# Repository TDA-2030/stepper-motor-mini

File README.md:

# Stepper Motor mini

A very simple and low-cost  stepper motor controller based on [dummy robot](https://gitee.com/switchpi/dummy)

## How to build

build on Windows

1. Download toolchain from https://github.com/xpack-dev-tools/arm-none-eabi-gcc-xpack/releases and unzip it.
2. run follow command to build
    ```shell
    mkdir build
    cmake -G "MinGW Makefiles" ..
    ```

## Feature

- Power: 12v~24v
- 2-layer board
- mini size
- Modbus support

## Preview

<center>
<figure>

·
·
·

</figure>
</center>

## Uasge

### Button Functions

| Action     | Function              |
| ---------- | --------------------- |
| click      | toggle to run or stop |
| long press | restore settings      |

### calibration

push down the button then power on, the motor well start to calibration sensor.

### Modbus Register

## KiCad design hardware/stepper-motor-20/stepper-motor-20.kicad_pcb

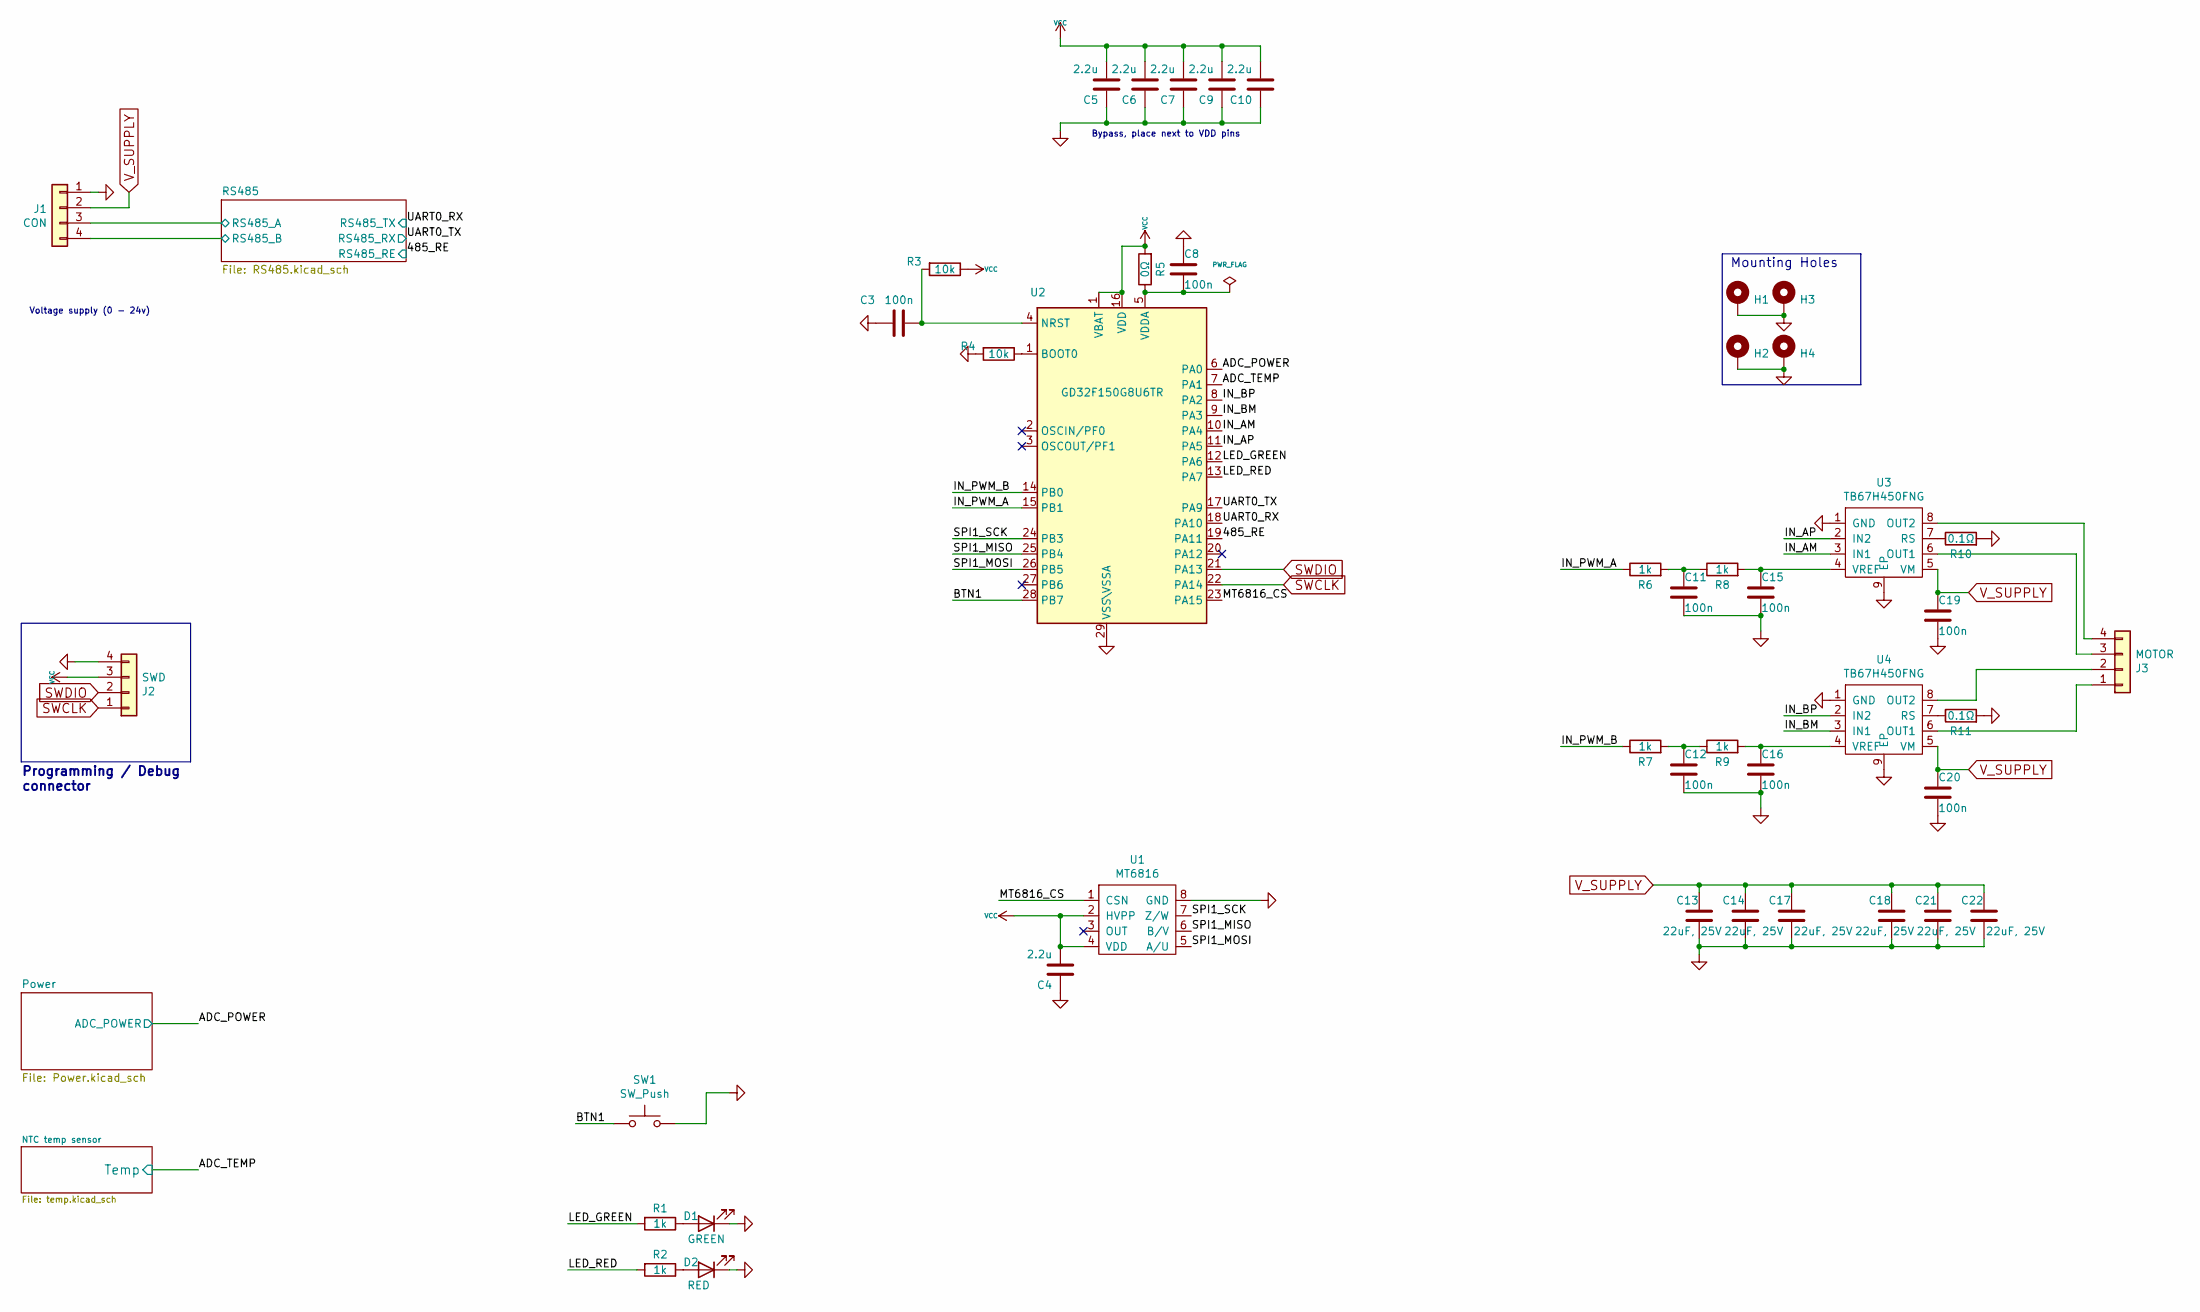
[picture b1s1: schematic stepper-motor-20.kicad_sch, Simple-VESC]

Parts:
C3, C8, C11, C12, C15, C16, C19, C20: 100n; C_0402_1005Metric
C4, C5, C6, C7, C9, C10: 2.2u; C_0402_1005Metric
C13, C14, C17, C18, C21, C22: 22uF, 25V; C_1206_3216Metric
D1: GREEN; LED_0402_1005Metric
D2: RED; LED_0402_1005Metric
H1, H2, H3, H4: MountingHole_Pad; MountingHole_2.0mm_Pad_Via
J1: CON; PinHeader_1x04_P2.00mm_Vertical
J2: SWD; PinHeader_1x04_P1.00mm_Vertical
J3: MOTOR; PinHeader_1x04_P2.00mm_Vertical
R1, R2, R6, R7, R8, R9: 1k; R_0402_1005Metric
R3, R4: 10k; R_0402_1005Metric
R5: 0Ω; R_0402_1005Metric
R10, R11: 0.1Ω; R_0805_2012Metric
SW1: SW_Push; SW_Push_SPST_NO_Alps_SKRK
U1: MT6816; SOP-8_3.76x4.96mm_P1.27mm
U2: GD32F150G8U6TR; QFN-28-1EP_4x4mm_P0.4mm_EP2.6x2.6mm
U3, U4: TB67H450FNG; SOIC-8-1EP_3.9x4.9mm_P1.27mm_EP2.41x3.3mm

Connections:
/485_RE: U2.19 (PA11); also elsewhere on the board
/ADC_POWER: U2.6 (PA0); also elsewhere on the board
/ADC_TEMP: U2.7 (PA1); also elsewhere on the board
/BTN1: SW1.1, U2.28 (PB7)
/IN_AM: U2.10 (PA4), U3.3 (IN1)
/IN_AP: U2.11 (PA5), U3.2 (IN2)
/IN_BM: U2.9 (PA3), U4.3 (IN1)
/IN_BP: U2.8 (PA2), U4.2 (IN2)
/IN_PWM_A: R6.1, U2.15 (PB1)
/IN_PWM_B: R7.1, U2.14 (PB0)
/LED_GREEN: R1.2, U2.12 (PA6)
/LED_RED: R2.2, U2.13 (PA7)
/MT6816_CS: U1.1 (CSN), U2.23 (PA15)
/RS485/RS485_A: J1.3; also elsewhere on the board
/RS485/RS485_B: J1.4; also elsewhere on the board
/SPI1_MISO: U1.6 (B/V), U2.25 (PB4)
/SPI1_MOSI: U1.5 (A/U), U2.26 (PB5)
/SPI1_SCK: U1.7 (Z/W), U2.24 (PB3)
/UART0_RX: U2.18 (PA10); also elsewhere on the board
/UART0_TX: U2.17 (PA9); also elsewhere on the board
unnamed: C3.2, R3.2, U2.4 (NRST)
unnamed: C8.1, R5.1, U2.5 (VDDA)
unnamed: C11.2, R6.2, R8.1
unnamed: C12.2, R7.2, R9.1
unnamed: C15.2, R8.2, U3.4 (VREF)
unnamed: C16.2, R9.2, U4.4 (VREF)
unnamed: D1.2 (A), R1.1
unnamed: D2.2 (A), R2.1
unnamed: J3.1, U4.6 (OUT1)
unnamed: J3.2, U4.8 (OUT2)
unnamed: J3.3, U3.6 (OUT1)
unnamed: J3.4, U3.8 (OUT2)
unnamed: R10.1, U3.7 (RS)
unnamed: R11.1, U4.7 (RS)
SWCLK: J2.1, U2.22 (PA14)
SWDIO: J2.2, U2.21 (PA13)
V_SUPPLY: C13.2, C14.2, C17.2, C18.2, C19.2, C20.2, C21.2, C22.2, J1.2, U3.5 (VM), U4.5 (VM); also elsewhere on the board

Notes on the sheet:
Programming / Debug connector
Voltage supply (0 - 24v)
Mounting Holes
Bypass, place next to VDD pins

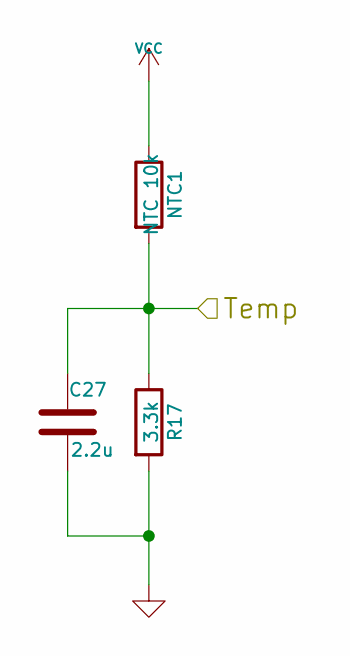
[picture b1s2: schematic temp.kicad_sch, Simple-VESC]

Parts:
C27: 2.2u; C_0402_1005Metric
NTC1: NTC 10k; R_0402_1005Metric
R17: 3.3k; R_0402_1005Metric

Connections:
/ADC_TEMP: C27.1, NTC1.2, R17.1; also elsewhere on the board

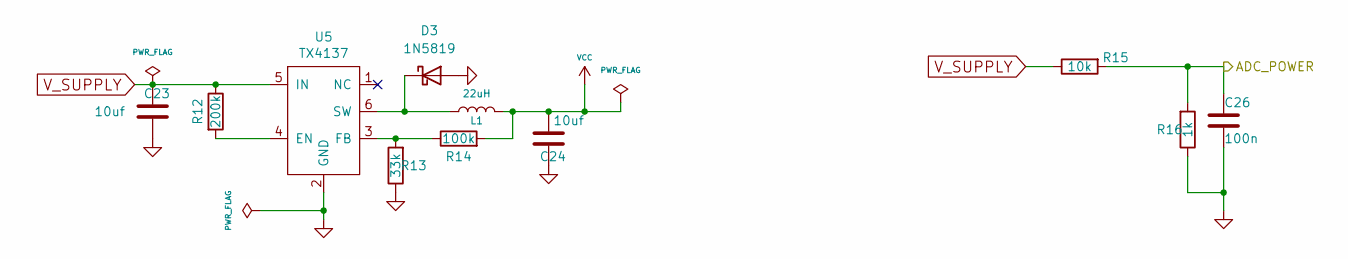
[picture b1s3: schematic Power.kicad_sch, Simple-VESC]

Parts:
C23, C24: 10uf; C_0603_1608Metric
C26: 100n; C_0402_1005Metric
D3: 1N5819; D_SOD-323
L1: 22uH; L_Taiyo-Yuden_MD-3030
R12: 200k; R_0402_1005Metric
R13: 33k; R_0402_1005Metric
R14: 100k; R_0402_1005Metric
R15: 10k; R_0402_1005Metric
R16: 1k; R_0402_1005Metric
U5: TX4137; SOT-23-6

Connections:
/ADC_POWER: C26.2, R15.2, R16.2; also elsewhere on the board
unnamed: D3.1 (K), L1.1, U5.6 (SW)
unnamed: R12.2, U5.4 (EN)
unnamed: R13.2, R14.1, U5.3 (FB)
V_SUPPLY: C23.2, R12.1, R15.1, U5.5 (IN); also elsewhere on the board

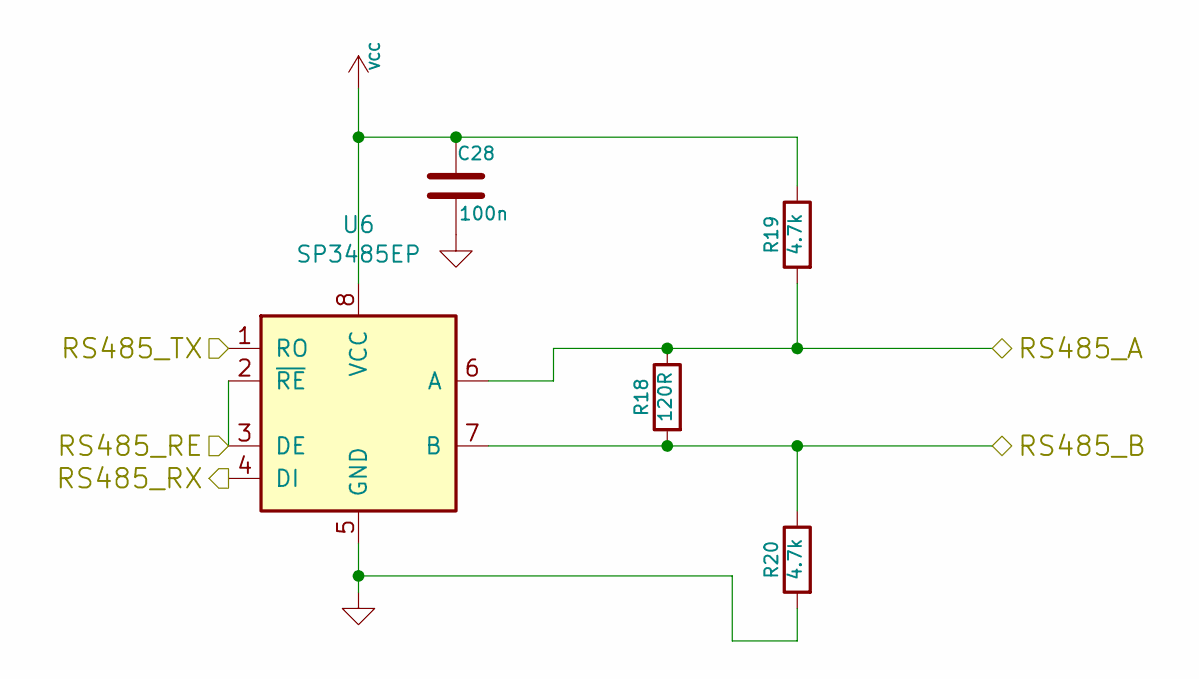
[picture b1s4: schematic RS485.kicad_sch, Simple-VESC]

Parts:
C28: 100n; C_0402_1005Metric
R18: 120R; R_0402_1005Metric
R19, R20: 4.7k; R_0402_1005Metric
U6: SP3485EP; SOIC-8_3.9x4.9mm_P1.27mm

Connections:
/485_RE: U6.2 (~RE), U6.3 (DE); also elsewhere on the board
/RS485/RS485_A: R18.1, R19.2, U6.6 (A); also elsewhere on the board
/RS485/RS485_B: R18.2, R20.1, U6.7 (B); also elsewhere on the board
/UART0_RX: U6.1 (RO); also elsewhere on the board
/UART0_TX: U6.4 (DI); also elsewhere on the board

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
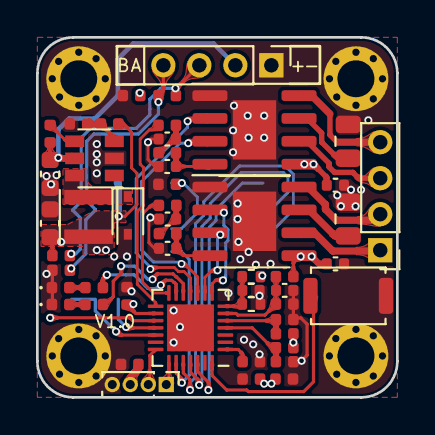
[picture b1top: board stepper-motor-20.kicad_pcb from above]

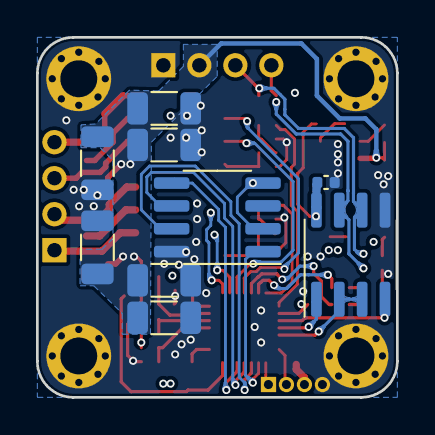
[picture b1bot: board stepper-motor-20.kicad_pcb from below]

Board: 4 copper layers, 20.0 x 20.0 mm, 64 parts (9 on the bottom side), 43 nets.

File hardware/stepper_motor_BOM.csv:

"Comment","Description","Designator","Footprint","LibRef","Pins","Quantity","PartNumber","url",
"15p","desc","C1,C2,","C_0402_1005Metric","libref","2","2","","",
"100n","desc","C3,C8,C11,C12,C15,C16,C19,C20,C28,C29,","C_0402_1005Metric","libref","2","10","","",
"2.2u","desc","C4,C5,C6,C7,C9,C10,C24,","C_0402_1005Metric","libref","2","7","","",
"10uf","desc","C25,C26,C27,","C_0603_1608Metric","libref","2","3","","",
"GREEN","desc","D1,","LED_0603_1608Metric","libref","2","1","","",
"RED","desc","D2,","LED_0603_1608Metric","libref","2","1","","",
"B5819W SL","desc","D3,","D_SOD-123","libref","2","1","","",
"22uH","desc","L1,","L_Taiyo-Yuden_NR-40xx","libref","2","1","","",
"1k","desc","R1,R2,R6,R7,R8,R9,R17,","R_0402_1005Metric","libref","2","7","","",
"10k","desc","R3,R4,R16,","R_0402_1005Metric","libref","2","3","","",
"0Ω","desc","R5,R21,R22,R23,","R_0402_1005Metric","libref","2","4","","",
"0.1Ω","desc","R10,R11,","R_0805_2012Metric","libref","2","2","","",
"3.3k","desc","R12,","R_0402_1005Metric","libref","2","1","","",
"200k","desc","R13,","R_0402_1005Metric","libref","2","1","","",
"33k","desc","R14,","R_0402_1005Metric","libref","2","1","","",
"100k","desc","R15,","R_0402_1005Metric","libref","2","1","","",
"120R","desc","R18,","R_0402_1005Metric","libref","2","1","","",
"360R","desc","R19,R20,","R_0402_1005Metric","libref","2","2","","",
"STM32F103CBTx","desc","U2,","LQFP-48_7x7mm_P0.5mm","libref","48","1","","",
"TB67H450FNG","desc","U3,U4,","SOIC-8-1EP_3.9x4.9mm_P1.27mm_EP2.41x3.3mm","libref","13","2","","",
"TX4137","desc","U5,","SOT-23-6","libref","6","1","","",
"8MHz","desc","Y1,","Crystal_SMD_3225-4Pin_3.2x2.5mm","libref","4","1","","",
"SW_Push","desc","SW2,SW3,","SW_Push_SPST_NO_Alps_SKRK","libref","2","2","","",
"22uF, 25V","desc","C13,C14,C17,C18,C21,C22,","C_1206_3216Metric","libref","2","6","","",
"MT6816","desc","U1,","SOIC-8_3.9x4.9mm_P1.27mm","libref","8","1","","",
"SP3485EP","desc","U6,","SOIC-8_3.9x4.9mm_P1.27mm","libref","8","1","","",
"NTC 10k","desc","NTC1,","R_0603_1608Metric","libref","2","1","","",
"Through Hole Items ",
"MountingHole_Pad","desc","H1,H2,H3,H4,","MountingHole_2.5mm_Pad_Via","libref","9","4","","",
"CON","desc","J1,","JST_PH_B4B-PH-K_1x04_P2.00mm_Vertical","libref","4","1","","",
"SWD","desc","J2,","PinHeader_1x04_P1.27mm_Vertical","libref","4","1","","",
"MOTOR","desc","J3,","PinHeader_1x04_P2.00mm_Vertical","libref","4","1","","",

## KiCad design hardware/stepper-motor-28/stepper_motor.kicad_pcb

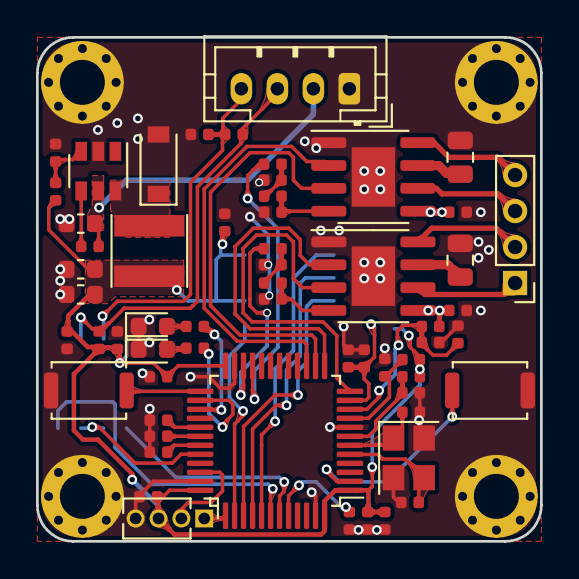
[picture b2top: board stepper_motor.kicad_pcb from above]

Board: 2 copper layers, 28.0 x 28.0 mm, 72 parts (0 on the bottom side), 49 nets.

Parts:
C1, C2: 15p; C_0402_1005Metric
C3, C8, C11, C12, C15, C16, C19, C20, C28, C29: 100n; C_0402_1005Metric
C4, C5, C6, C7, C9, C10, C24: 2.2u; C_0402_1005Metric
C13, C14, C17, C18, C21, C22: 22uF, 25V; C_1206_3216Metric
C25, C26, C27: 10uf; C_0603_1608Metric
D1: GREEN; LED_0603_1608Metric
D2: RED; LED_0603_1608Metric
D3: B5819W SL; D_SOD-123
H1, H2, H3, H4: MountingHole_Pad; MountingHole_2.5mm_Pad_Via
J1: CON; JST_PH_B4B-PH-K_1x04_P2.00mm_Vertical
J2: SWD; PinHeader_1x04_P1.27mm_Vertical
J3: MOTOR; PinHeader_1x04_P2.00mm_Vertical
L1: 22uH; L_Taiyo-Yuden_NR-40xx
NTC1: NTC 10k; R_0603_1608Metric
R1, R2, R6, R7, R8, R9, R17: 1k; R_0402_1005Metric
R3, R4, R16: 10k; R_0402_1005Metric
R5, R21, R22, R23: 0Ω; R_0402_1005Metric
R10, R11: 0.1Ω; R_0805_2012Metric
R12: 3.3k; R_0402_1005Metric
R13: 200k; R_0402_1005Metric
R14: 33k; R_0402_1005Metric
R15: 100k; R_0402_1005Metric
R18: 120R; R_0402_1005Metric
R19, R20: 360R; R_0402_1005Metric
SW2, SW3: SW_Push; SW_Push_SPST_NO_Alps_SKRK
U1: MT6816; SOIC-8_3.9x4.9mm_P1.27mm
U2: STM32F103CBTx; LQFP-48_7x7mm_P0.5mm
U3, U4: TB67H450FNG; SOIC-8-1EP_3.9x4.9mm_P1.27mm_EP2.41x3.3mm
U5: TX4137; SOT-23-6
U6: SP3485EP; SOIC-8_3.9x4.9mm_P1.27mm
Y1: 8MHz; Crystal_SMD_3225-4Pin_3.2x2.5mm

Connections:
/485_RE: U2.32, U6.2, U6.3
/ADC_POWER: C28.2, R16.2, R17.2, U2.10
/ADC_TEMP: C24.1, NTC1.2, R12.1, U2.11
/BTN1: SW3.1, U2.25
/BTN2: SW2.1, U2.2
/ID0: R21.1, U2.29
/ID1: R22.1, U2.30
/ID2: R23.1, U2.31
/IN_AM: U2.14, U3.3
/IN_AP: U2.15, U3.2
/IN_BM: U2.12, U4.3
/IN_BP: U2.13, U4.2
/IN_PWM_A: R6.1, U2.21
/IN_PWM_B: R7.1, U2.22
/LED_GREEN: R1.2, U2.26
/LED_RED: R2.2, U2.27
/MT6816_CS: U1.1, U2.38
/RS485/RS485_A: J1.3, R18.1, R19.2, U6.6
/RS485/RS485_B: J1.4, R18.2, R20.1, U6.7
/SPI1_MISO: U1.6, U2.40
/SPI1_MOSI: U1.5, U2.41
/SPI1_SCK: U1.7, U2.39
/UART1_RX: U2.43, U6.1
/UART1_TX: U2.42, U6.4
GND: C1.2, C2.2, C3.1, C4.1, C5.1, C6.1, C7.1, C8.2, C9.1, C10.1, C11.1, C12.1, C13.1, C14.1, C15.1, C16.1, C17.1, C18.1, C19.1, C20.1, C21.1, C22.1, C24.2, C25.1, C26.1, C27.1, C28.1, C29.2, D1.1, D2.1, D3.2, H1.1, H2.1, H3.1, H4.1, J1.1, J2.4, R4.2, R10.2, R11.2, R12.2, R14.1, R17.1, R20.2, R21.2, R22.2, R23.2, SW2.2, SW3.2, U1.8, U2.8, U2.23, U2.35, U2.47, U3.1, U3.9, U4.1, U4.9, U5.2, U6.5, Y1.2, Y1.4
unnamed: C1.1, U2.6, Y1.1
unnamed: C2.1, U2.5, Y1.3
unnamed: C3.2, R3.2, U2.7
unnamed: C8.1, R5.1, U2.9
unnamed: C11.2, R6.2, R8.1
unnamed: C12.2, R7.2, R9.1
unnamed: C15.2, R8.2, U3.4
unnamed: C16.2, R9.2, U4.4
unnamed: D1.2, R1.1
unnamed: D2.2, R2.1
unnamed: D3.1, L1.1, U5.6
unnamed: J3.1, U4.6
unnamed: J3.2, U4.8
unnamed: J3.3, U3.6
unnamed: J3.4, U3.8
unnamed: R4.1, U2.44
unnamed: R10.1, U3.7
unnamed: R11.1, U4.7
unnamed: R13.2, U5.4
unnamed: R14.2, R15.1, U5.3
SWCLK: J2.1, U2.37
SWDIO: J2.2, U2.34
VCC: C4.2, C5.2, C6.2, C7.2, C9.2, C10.2, C26.2, C27.2, C29.1, J2.3, L1.2, NTC1.1, R3.1, R5.2, R15.2, R19.1, U1.2, U1.4, U2.1, U2.24, U2.36, U2.48, U6.8
V_SUPPLY: C13.2, C14.2, C17.2, C18.2, C19.2, C20.2, C21.2, C22.2, C25.2, J1.2, R13.1, R16.1, U3.5, U4.5, U5.5

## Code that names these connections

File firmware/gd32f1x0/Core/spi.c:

/**************************************************************************//**
  \file     spi.c
  \brief    this file contains the initialization of SPI peripherals and
            the code implementation of reading and writing half words.
  \author   Lao·Zhu
  \version  V1.0.2
  \date     29. October 2021
 ******************************************************************************/

#include "spi.h"
#include "gd32f1x0.h"

/*!
    \brief      spi0 transmit data for sc60228
    \param[in]  data: data to transmit
    \retval     data received from slave
*/
unsigned short spi_readwrite_halfworld(unsigned short data) {
    unsigned short buffer;
    while (RESET == spi_i2s_flag_get(SPI0, SPI_FLAG_TBE));

    /* send this data through spi0 */
    spi_i2s_data_transmit(SPI0, data);
    while (RESET == spi_i2s_flag_get(SPI0, SPI_FLAG_RBNE));

    /* get data received through spi0 */
    buffer = spi_i2s_data_receive(SPI0);
    return buffer;
}

void spi_cs_enable()
{
    gpio_bit_reset(GPIOA, GPIO_PIN_15);
}

void spi_cs_disable()
{
    gpio_bit_set(GPIOA, GPIO_PIN_15);
}

/*!
    \brief configure spi0 periph and its gpios
*/
void spi_config(void) {
    spi_parameter_struct spi_init_struct;

    /* enable GPIO clock and SPI0 clock*/
    rcu_periph_clock_enable(RCU_GPIOB);
    rcu_periph_clock_enable(RCU_SPI0);

    /* SPI0 GPIO config: SCK/PB3, MISO/PB4, MOSI/PB5 */
    gpio_af_set(GPIOB, GPIO_AF_0, GPIO_PIN_3 | GPIO_PIN_4 | GPIO_PIN_5);
    gpio_mode_set(GPIOB, GPIO_MODE_AF, GPIO_PUPD_NONE, GPIO_PIN_3 | GPIO_PIN_4 | GPIO_PIN_5);
    gpio_output_options_set(GPIOB, GPIO_OTYPE_PP, GPIO_OSPEED_50MHZ, GPIO_PIN_3 | GPIO_PIN_4 | GPIO_PIN_5);

    /* SPI0 GPIO config: CS/PA15 */
    gpio_mode_set(GPIOA, GPIO_MODE_OUTPUT, GPIO_PUPD_NONE, GPIO_PIN_15);
    gpio_output_options_set(GPIOA, GPIO_OTYPE_PP, GPIO_OSPEED_50MHZ, GPIO_PIN_15);

    /* pull up CS pin to end sending data */
    gpio_bit_set(GPIOA, GPIO_PIN_15);

    /* SPI0 parameter config */
    spi_init_struct.trans_mode = SPI_TRANSMODE_FULLDUPLEX;
    spi_init_struct.device_mode = SPI_MASTER;
    spi_init_struct.frame_size = SPI_FRAMESIZE_16BIT;
    spi_init_struct.clock_polarity_phase = SPI_CK_PL_HIGH_PH_2EDGE;
    spi_init_struct.nss = SPI_NSS_SOFT;
    spi_init_struct.prescale = SPI_PSC_4;
    spi_init_struct.endian = SPI_ENDIAN_MSB;
    spi_crc_off(SPI0);
    spi_init(SPI0, &spi_init_struct);

    /* SPI0 enable */
    spi_enable(SPI0);
}

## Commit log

2024-01-01 add firmware
2024-01-01 firmware: update
2024-01-02 add motor-20 pcb
2024-01-21 add freemodbus
2024-01-21 add gd32f130 target
2024-01-21 gd32: update
2024-01-21 add reduce sensor resolution
2024-01-21 add modbus
2024-01-21 update reg
2024-01-21 stm32: reduce time of spi transmition
2024-03-04 add reverse direction
2024-03-18 add temperature and voltage threshold
